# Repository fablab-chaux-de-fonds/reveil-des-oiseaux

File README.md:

# Le réveil des oiseaux
En combinant une boîte qui diffuse le cri d'un oiseau avec des excursions ornithologiques, des petits déjeuners conviviaux et des ateliers interactifs, notre projet vise à créer une journée dédiée à la découverte et à la célébration des merveilles aviaires, tout en sensibilisant à la préservation de la biodiversité.

<div align="center">

</div>

# Liste des pièces
| | |
| ----------- | ----------- |
||Le [DFPlayer Pro](https://wiki.dfrobot.com/DFPlayer_PRO_SKU_DFR0768) est un mini lecteur MP3 polyvalent, offrant quatre modes de contrôle : Arduino, commande AT, boutons intégrés et ADKEY. Avec 128 Mo de stockage intégré et un connecteur Type-C, il est facile à utiliser et offre une meilleure qualité audio. En outre, il propose des fonctions avancées telles que l'avance rapide, le retour rapide et la lecture à partir d'un point spécifique dans le fichier audio.
|| [Adafruit-1314](https://www.adafruit.com/product/1314) - Le haut-parleur de 3 pouces de diamètre est spécialement conçu pour offrir une impédance de 4 ohms et une puissance maximale de 3 watts. Ce haut-parleur est idéal pour une variété de projets audio où une qualité sonore fiable est essentielle. Son cône de haut-parleur de 3 pouces offre un son clair et précis, tandis que ses 4 supports de montage pratiques, espacés de 60 mm, facilitent son installation dans différentes configurations.
||L'extension de câble USB-C mâle vers femelle offre une connectivité pratique pour vos appareils USB-C. Avec ses 20 cm de longueur, ce câble compact prend en charge la transmission rapide de données et le chargement évolutif.
||Le bouton de pression mini R13-507 de Sesaat est conçu pour offrir une fonction de réinitialisation fiable dans les panneaux électriques de 16 mm. Avec ses 2 broches, il offre une puissance de 3A à 250VAC, garantissant une performance sécurisée et durable. Parfait pour les applications nécessitant un bouton compact et fiable.
||Ce bouton poussoir LED transparent offre un éclairage coloré et interactif pour les enfants. Fabriqué en plastique ABS de haute qualité, il est durable et résistant aux chocs.
||Le connecteur JST PH2 est une solution fiable pour les connexions électriques. Avec ses fils pré-soudés et son format compact, il offre une installation facile et sécurisée. Parfait pour les projets électroniques nécessitant une connexion stable et durable.
|| Un kit de vis d'espacement à tête plate hexagonale, M2, fabriqué en plastique et nylon, incluant des écrous assortis.

# PCB
Le PCB est réalisé avec [KiCAD](https://www.kicad.org/). Les projet se trouve dans le dossier [kicad](./kicad)
| | |
| --- | --- |
| |  |

# Assemblage
Le boîtier est réaliser avec [OpenSCAD](https://openscad.org/), à l'aide du repo [OpenSCADBoxes](https://github.com/daci6920/OpenSCADBoxes/tree/master). Le boîtier est découpé dans du multipli 4mm à l'aide d'une découpeuse laser et de [fichier de design](./enclosure/box.svg).

| | | | 
| --- | --- | --- |
| |   | |

:camera: [Raphaël Monnard](https://github.com/raphaelmonnard/)

# Son
Les sons previennent du site https://www.vogelwarte.ch/ - La Station ornithologique suisse

# Evènement
[Muzoo](https://muzoo.ch/evenement/reveil-oiseaux-2024/): Le réveil des oiseaux | Le 5 mai 2024

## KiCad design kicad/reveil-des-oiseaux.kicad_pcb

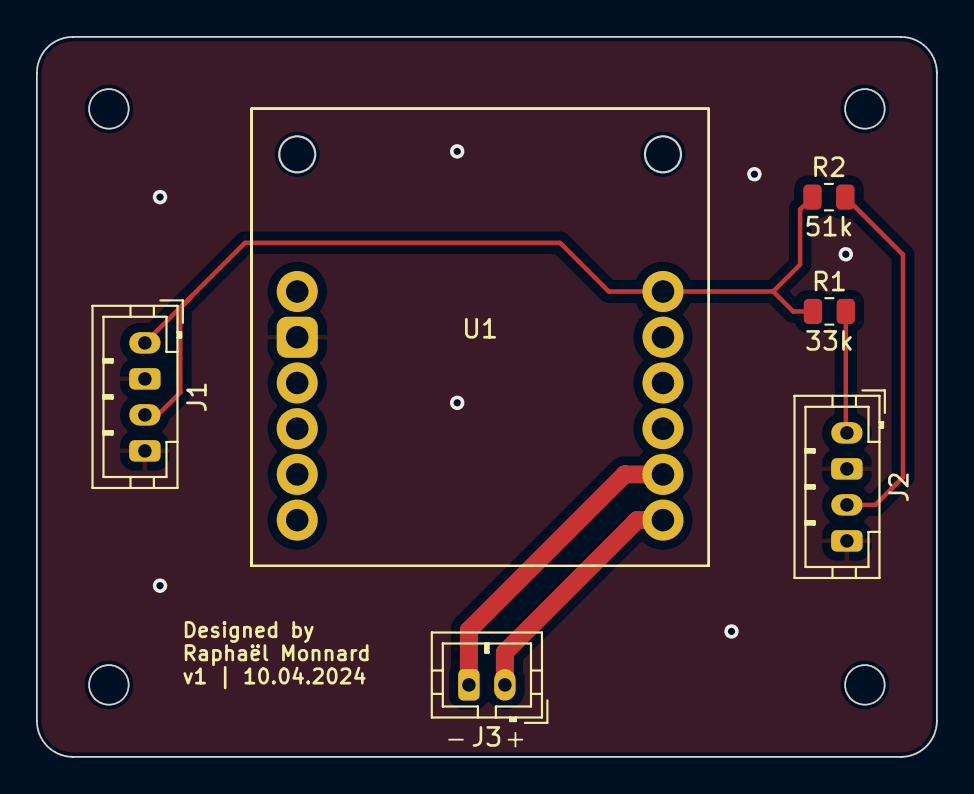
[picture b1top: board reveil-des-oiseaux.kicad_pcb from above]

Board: 2 copper layers, 50.0 x 40.0 mm, 6 parts (0 on the bottom side), 6 nets.

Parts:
J1, J2: Conn_01x04_Pin; JST_PH_B4B-PH-K_1x04_P2.00mm_Vertical
J3: Conn_01x02_Pin; JST_PH_B2B-PH-K_1x02_P2.00mm_Vertical
R1: 33k; R_0805_2012Metric
R2: 51k; R_0805_2012Metric
U1: DFR0768

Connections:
/KEY: J1.1, J1.3, R1.1, R2.1, U1.7 (KEY)
/Speaker +: J3.1, U1.12 (L+)
/Speaker -: J3.2, U1.11 (L-)
GND: J1.2, J1.4, J2.2, J2.4, U1.2 (GND)
unnamed: J2.1, R1.2
unnamed: J2.3, R2.2

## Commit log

2024-04-09 add BOM
2024-04-13 add kicad
2024-04-17 add enclosure file
2024-05-05 Finalisation de la doc
2024-05-05 fix render
